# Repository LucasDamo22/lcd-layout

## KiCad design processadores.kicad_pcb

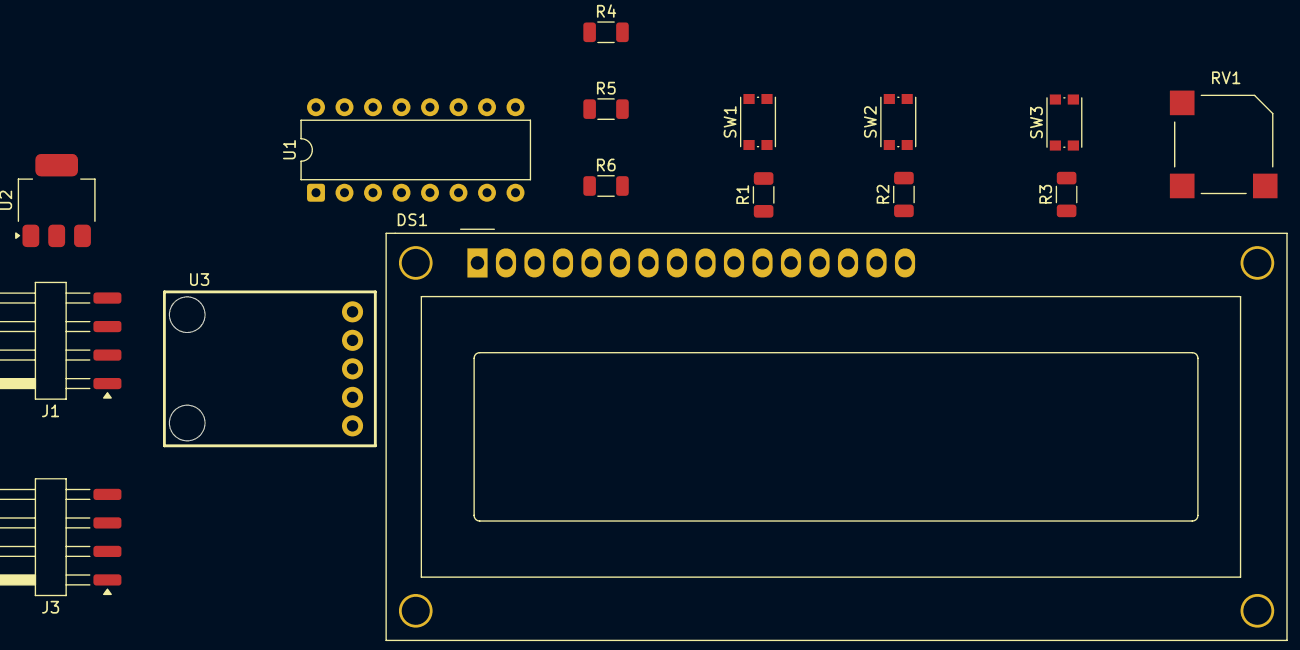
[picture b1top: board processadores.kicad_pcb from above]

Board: 2 copper layers, 16 parts (0 on the bottom side), 17 nets.

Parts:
DS1: WC1602A
J1, J3: Conn_01x04_Pin; Harwin_M20-89004xx_1x04_P2.54mm_Horizontal
R1, R2, R3: 10K; R_1206_3216Metric
R4, R5, R6: 4K7; R_1206_3216Metric
RV1: R_Potentiometer; MagneticBuzzer_Kobitone_254-EMB84Q-RO
SW1, SW2, SW3: SW_Push; SW_Push_1P1T_NO_CK_KMR2
U1: PCF8574AP; DIP-16_W7.62mm
U2: AMS1117; SOT-223-3_TabPin2
U3: HMC5883L

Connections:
+3.3V: R4.1, R5.1, U1.16 (VDD), U2.2 (VO), U3.1 (VCC)
+5V: DS1.2 (VDD), J1.4, R1.1, R2.1, R3.1, R6.1, RV1.3, U2.3 (VI)
E: DS1.6 (E), U1.6 (P2)
GND: DS1.1 (VSS), DS1.16 (LED(-)), J1.1, J3.1, RV1.1, SW1.1, SW2.1, SW3.1, U1.1 (A0), U1.2 (A1), U1.3 (A2), U1.8 (GND), U2.1 (ADJ), U3.2 (GND)
unnamed: DS1.11 (D4), U1.9 (P4)
unnamed: DS1.12 (D5), U1.10 (P5)
unnamed: DS1.13 (D6), U1.11 (P6)
unnamed: DS1.14 (D7), U1.12 (P7)
unnamed: DS1.15 (LED(+)), R6.2
unnamed: DS1.3 (VO), RV1.2
unnamed: J1.2, R5.2, U1.15 (SDA), U3.4 (SDA)
unnamed: J1.3, R4.2, U1.14 (SCL), U3.3 (SCL)
RS: DS1.4 (RS), U1.4 (P0)
R/W: DS1.5 (R/W), U1.5 (P1)
SW1: J3.4, R1.2, SW1.2
SW2: J3.3, R2.2, SW2.2
SW3: J3.2, R3.2, SW3.2

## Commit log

2026-06-30 saving progress
